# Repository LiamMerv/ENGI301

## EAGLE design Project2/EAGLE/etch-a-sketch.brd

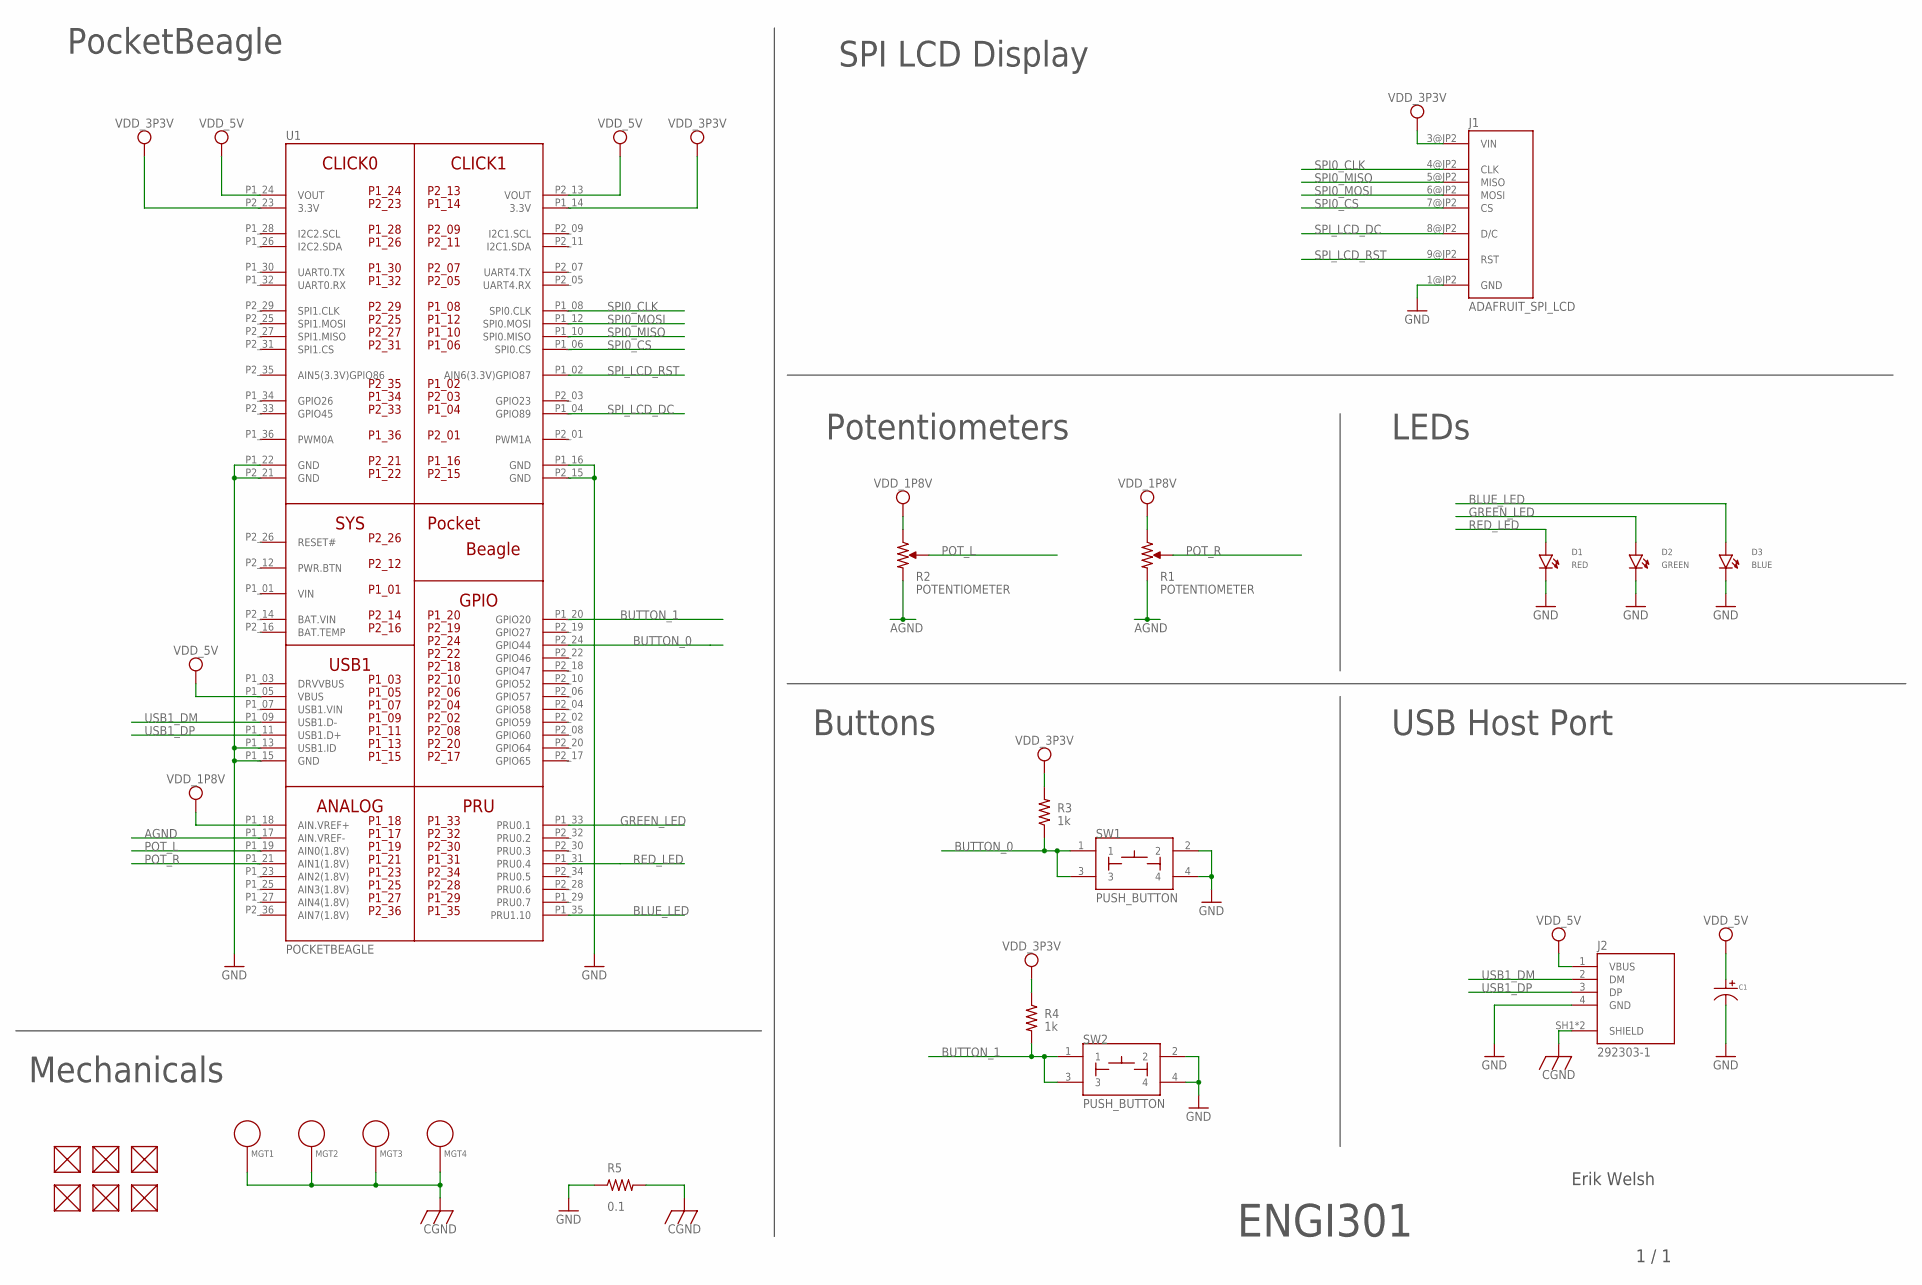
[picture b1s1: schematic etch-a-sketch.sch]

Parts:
C1: CAPACITOR_P_10MM; CP10MM
D1: RED; EIA-STD
D2: GREEN; EIA-STD
D3: BLUE; EIA-STD
FUD1, FUD2, FUD3, FUD4, FUD5, FUD6: FIDUCIAL; FIDUCIAL_40MIL
J1: ADAFRUIT_SPI_LCD; SPI_LCD_DISPLAY
J2: 292303-1; TE_292303-1
MGT1, MGT2, MGT3, MGT4: MOUNTING_HOLE
R1, R2: POTENTIOMETER; POT-PO90S
R3, R4: 1k; R0603
R5: 0.1; R0805
SW1, SW2: PUSH_BUTTON; BUTTON_12.5MM
U1: POCKETBEAGLE

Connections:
AGND: R1.CW, R2.CW, U1.P1_17 (AIN.VREF-)
BAT.VIN: U1.P2_14 (BAT.VIN)
BLUE_LED: D3.ANODE, U1.P1_35 (PRU1.10)
BUTTON_0: R3.1, SW1.1, SW1.3, U1.P2_24 (GPIO44)
BUTTON_1: R4.2, SW2.1, SW2.3, U1.P1_20 (GPIO20)
CGND: J2.SH1 (SHIELD), J2.SH2 (SHIELD), MGT1.P$1, MGT2.P$1, MGT3.P$1, MGT4.P$1, R5.2
GND: C1.P$2, D1.CATHODE, D2.CATHODE, D3.CATHODE, J1.1@JP2 (GND), J2.4 (GND), R5.1, SW1.2, SW1.4, SW2.2, SW2.4, U1.P1_13 (USB1.ID), U1.P1_15 (GND), U1.P1_16 (GND), U1.P1_22 (GND), U1.P2_15 (GND), U1.P2_21 (GND)
GREEN_LED: D2.ANODE, U1.P1_33 (PRU0.1)
POT_L: R2.S, U1.P1_19 (AIN0(1.8V))
POT_R: R1.S, U1.P1_21 (AIN1(1.8V))
RED_LED: D1.ANODE, U1.P1_31 (PRU0.4)
SPI0_CLK: J1.4@JP2 (CLK), U1.P1_08 (SPI0.CLK)
SPI0_CS: J1.7@JP2 (CS), U1.P1_06 (SPI0.CS)
SPI0_MISO: J1.5@JP2 (MISO), U1.P1_10 (SPI0.MISO)
SPI0_MOSI: J1.6@JP2 (MOSI), U1.P1_12 (SPI0.MOSI)
SPI_LCD_DC: J1.8@JP2 (D/C), U1.P1_04 (GPIO89)
SPI_LCD_RST: J1.9@JP2 (RST), U1.P1_02 (AIN6(3.3V)GPIO87)
USB1_DM: J2.2 (DM), U1.P1_09 (USB1.D-)
USB1_DP: J2.3 (DP), U1.P1_11 (USB1.D+)
VDD_1P8V: R1.CCW, R2.CCW, U1.P1_18 (AIN.VREF+)
VDD_3P3V: J1.3@JP2 (VIN), R3.2, R4.1, U1.P2_23 (3.3V)
VDD_5V: C1.P$1, J2.1 (VBUS), U1.P1_05 (VBUS), U1.P1_24 (VOUT), U1.P2_13 (VOUT)
VIN: U1.P1_01 (VIN)

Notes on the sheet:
SPI LCD Display
Potentiometers
LEDs
Buttons
USB Host Port
PocketBeagle
Mechanicals
ENGI301
1 / 1
Erik Welsh

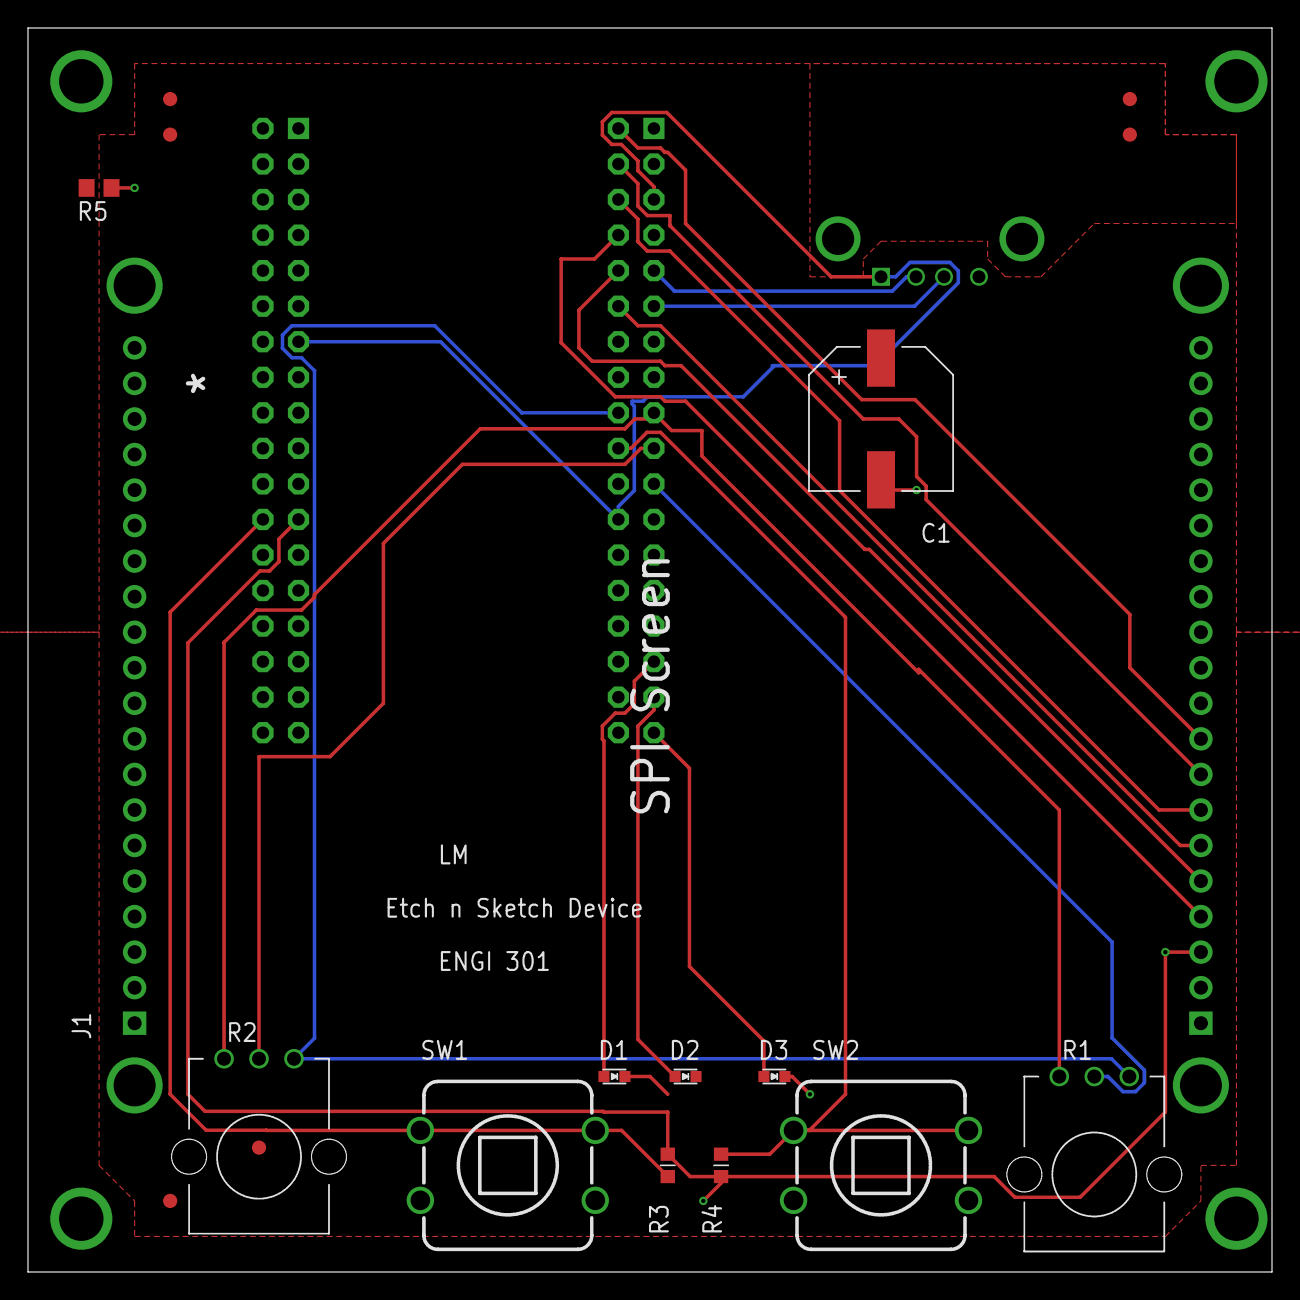
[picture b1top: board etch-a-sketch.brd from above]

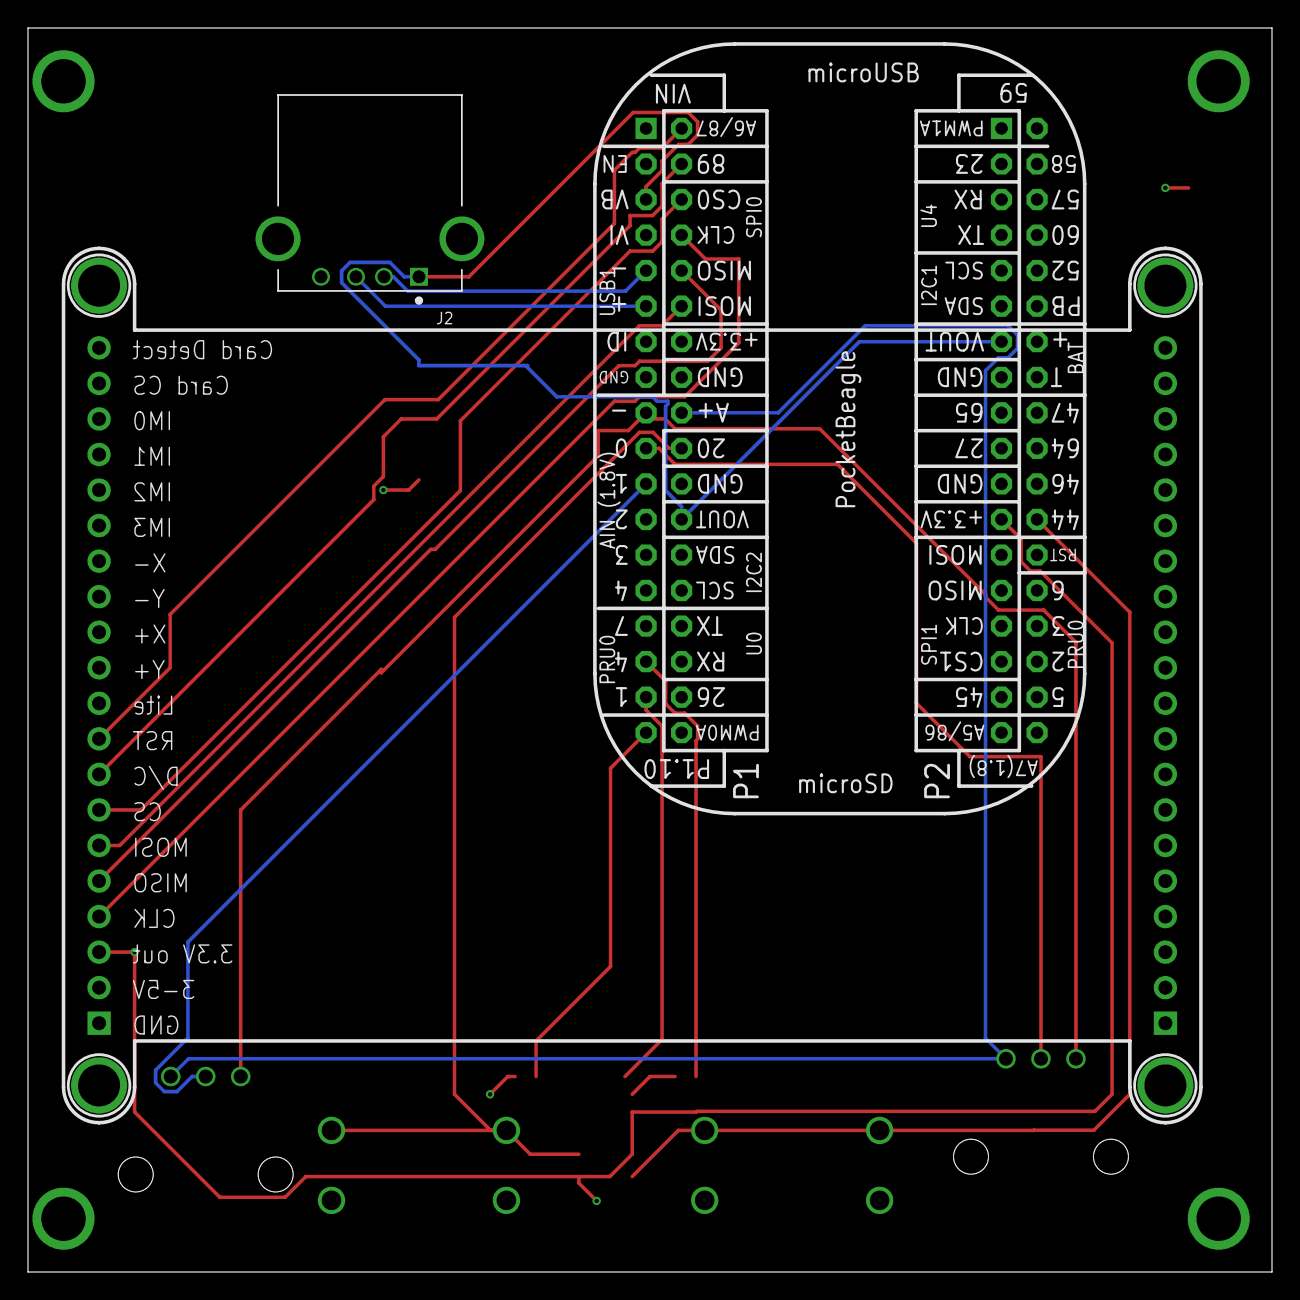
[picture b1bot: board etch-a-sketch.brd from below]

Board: 4 copper layers, 88.9 x 88.9 mm, 24 parts (2 on the bottom side), 21 nets.

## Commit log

2022-09-24 Simple Calculator
2022-09-24 Blink LED
2023-01-11 main script py
2023-01-13 Rename Plant.lbr to etchnsketch.lbr
2023-01-13 Rename etchnsketch.lbr to etch-a-sketch.lbr
